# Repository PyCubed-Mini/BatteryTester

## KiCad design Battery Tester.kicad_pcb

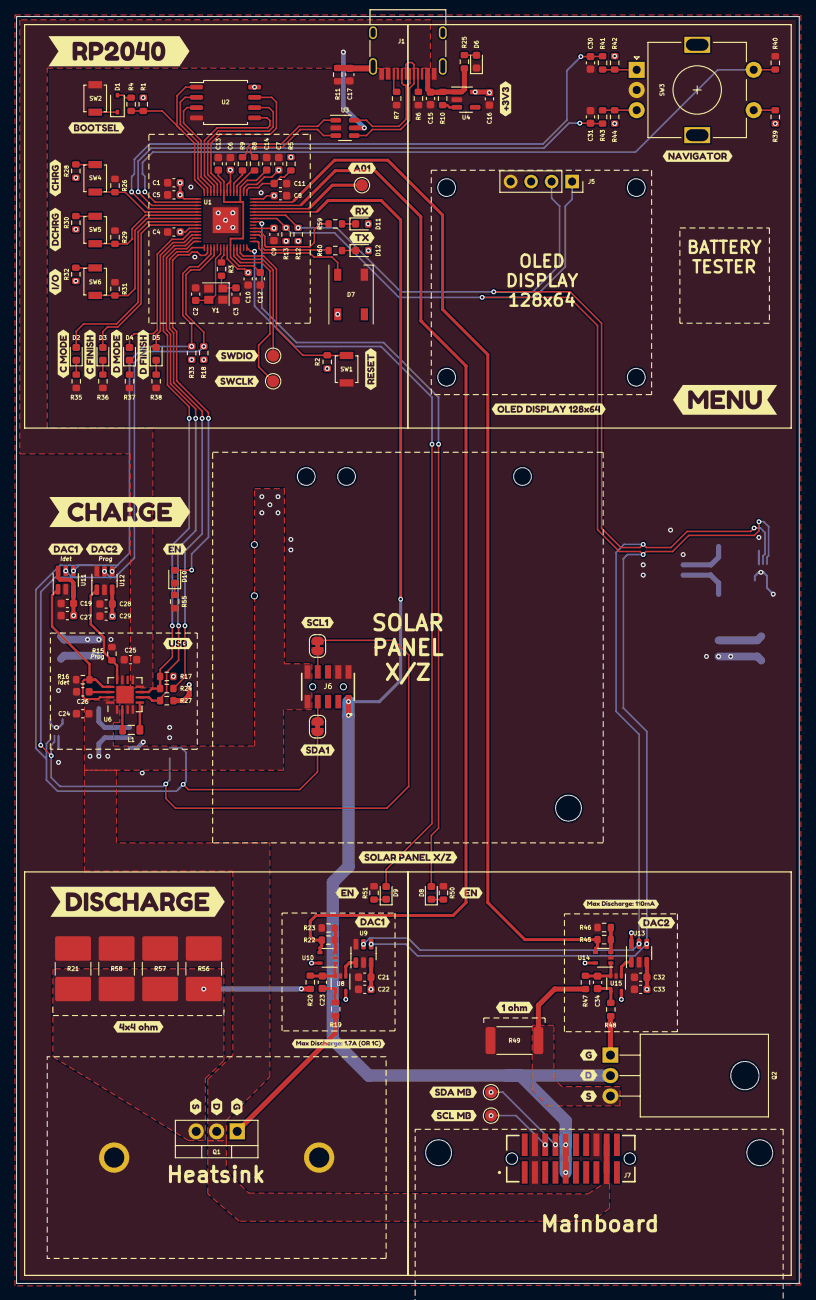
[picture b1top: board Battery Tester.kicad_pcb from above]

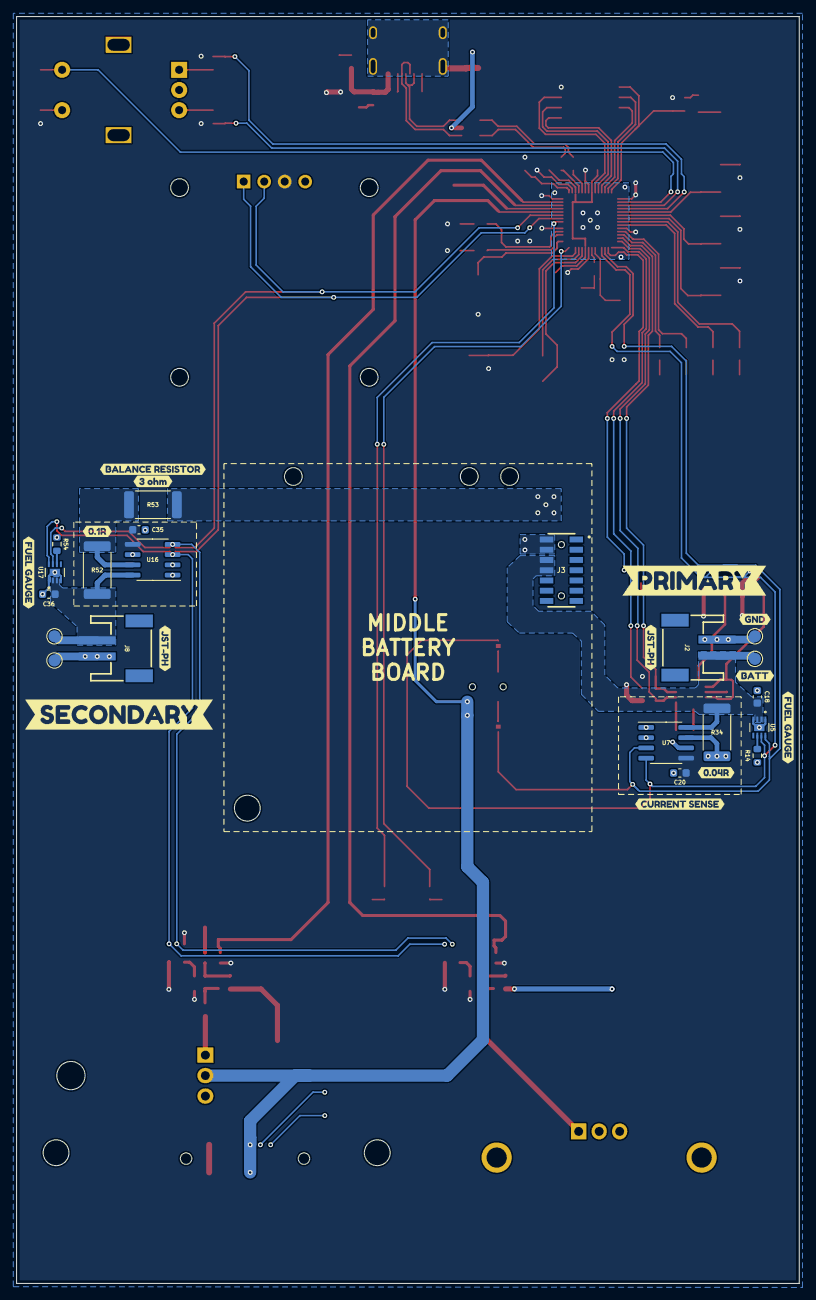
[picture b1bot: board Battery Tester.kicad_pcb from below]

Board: 2 copper layers, 97.0 x 157.0 mm, 212 parts (33 on the bottom side), 99 nets.

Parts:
C1, C11, C12, C15, C16, C18, C36: 1uF; C_0603_1608Metric
C2, C3: 22pF; C_0603_1608Metric
C4, C5, C6, C7, C8, C9, C10, C13, C14, C19, C20, C21, C26, C28, C32, C35: 0.1uF; C_0603_1608Metric
C17: 4.7nF; C_0603_1608Metric
C22, C23, C24, C25, C27, C29, C33, C34: 10uF; C_0603_1608Metric
C30, C31: 0.01uF; C_0603_1608Metric
D1: D_Schottky; D_SOD-323
D2, D3, D4, D5, D11, D12: Amber; LED_0603_1608Metric
D6: Green; LED_0603_1608Metric
D7: WS2812B; LED_WS2812B_PLCC4_5.0x5.0mm_P3.2mm
D8, D9, D10: Blue; LED_0603_1608Metric
HS2: Heatsink_Pad; RAT2X38E
J1: USB-C Receptacle; USB_C_Receptacle_HRO_TYPE-C-31-M-12
J2, J8: JST-PH; JSTPH2
J3: FLE-107-01-X-DV-A; SAMTEC_FLE-107-01-X-DV-A
J5: OLED DISPLAY; PinSocket_1x04_P2.54mm_Vertical
J6: FLE-105-01-X-DV-A; SAMTEC_FLE-105-01-X-DV-A
J7: TFM-110-12-X-D-A; SAMTEC_TFM-110-12-X-D-A
JP1, JP2: Jumper_2_Bridged; SolderJumper-2_P1.3mm_Bridged_RoundedPad1.0x1.5mm
L1: L_Small; L_0805_2012Metric
Q1: IRF540N; TO-220-3_Vertical
Q2: IRF540N; TO-220-3_Horizontal_TabDown
R1, R2, R12, R13, R14, R18, R26, R27, R29, R31, R33, R40, R41, R42, R43, R44, R54: 10K; R_0603_1608Metric
R3, R4, R23, R25, R35, R36, R37, R38, R46, R50, R51, R55, R59, R60: 1K; R_0603_1608Metric
R5, R19, R20, R22, R45, R47, R48: 0; R_0603_1608Metric
R6, R7: 5.1K; R_0603_1608Metric
R8, R9: 27.4; R_0603_1608Metric
R10: 100K; R_0603_1608Metric
R11: 1M; R_0603_1608Metric
R15: R_prog; R_0603_1608Metric
R16: R_idet; R_0603_1608Metric
R17: 390R; R_0603_1608Metric
R21, R56, R57, R58: 4; R_2816_7142Metric
R24, R28, R30, R32, R39: 2K; R_0603_1608Metric
R34: 0.04R; R_2512_6332Metric
R49: 1; R_2512_6332Metric
R52: 0.1R; R_2512_6332Metric
R53: 3R; R_2512_6332Metric
Ref**: Val**; pycubed_mini_half
SW1: Reset; SW_SPST_B3U-1000P
SW2: BOOTSEL; SW_SPST_B3U-1000P
SW3: RotaryEncoder_Switch; RotaryEncoder_Alps_EC11E-Switch_Vertical_H20mm
SW4: Start/Stop; SW_SPST_B3U-1000P
SW5: Charge; SW_SPST_B3U-1000P
SW6: Discharge; SW_SPST_B3U-1000P
TP1: SCL1_MB; TestPoint_Pad_D1.5mm
TP2: SDA1_MB; TestPoint_Pad_D1.5mm
TP3: SWDIO; TestPoint_Pad_D1.5mm
TP4: SWCLK; TestPoint_Pad_D1.5mm
TP5: A01; TestPoint_Pad_D1.5mm
TP6: BATT_SENS; TestPoint_Pad_D1.5mm
TP7, TP9: GND; TestPoint_Pad_D1.5mm
TP8: BATT_SENS_2; TestPoint_Pad_D1.5mm
U1: RP2040; IC57_RP2040
U2: W25Q32JVSS; SOIC-8_5.23x5.23mm_P1.27mm
U3: USBLC6-2SC6; SOT-23-6
U4: AP2112K-3.3; SOT-23-5
U5, U17: MAX17048G
U6: LTC4001; QFN-16-1EP_4x4mm_P0.65mm_EP2.15x2.15mm
U7, U16: INA219BxD; SOIC-8_3.9x4.9mm_P1.27mm
U8, U10, U14, U15: TLV9001IDCK; SOT-353_SC-70-5
U9, U11, U12, U13: MCP4725xxx-xCH; SOT-23-6
Y1: 12MHz; Crystal_SMD_2520-4Pin_2.5x2.0mm
kibuzzard-643A0FFF: G***; kibuzzard-643A0FFF
kibuzzard-643A06C8: G***; kibuzzard-643A06C8
kibuzzard-643A08B7: G***; kibuzzard-643A08B7
kibuzzard-643A09FA, kibuzzard-643A09FA#2, kibuzzard-643A09FA#3: G***; kibuzzard-643A09FA
kibuzzard-643A070F: G***; kibuzzard-643A070F
kibuzzard-643A089C: G***; kibuzzard-643A089C
kibuzzard-643A091C: G***; kibuzzard-643A091C
kibuzzard-643A0700, kibuzzard-643A0700#2: G***; kibuzzard-643A0700
kibuzzard-643A0912: G***; kibuzzard-643A0912
kibuzzard-643CBBC0: G***; kibuzzard-643CBBC0
kibuzzard-6438A1B5: G***; kibuzzard-6438A1B5
kibuzzard-6438A1DA: G***; kibuzzard-6438A1DA
kibuzzard-6438A1E8: G***; kibuzzard-6438A1E8
kibuzzard-6438A2F8: G***; kibuzzard-6438A2F8
kibuzzard-6438A03B: G***; kibuzzard-6438A03B
kibuzzard-6438A05A: G***; kibuzzard-6438A05A
kibuzzard-6438A06A: G***; kibuzzard-6438A06A
kibuzzard-6438A12F: G***; kibuzzard-6438A12F
kibuzzard-6438A59C: G***; kibuzzard-6438A59C
kibuzzard-6438A119: G***; kibuzzard-6438A119
kibuzzard-6438A146: G***; kibuzzard-6438A146
kibuzzard-6438A591: G***; kibuzzard-6438A591
kibuzzard-6438B7A5: G***; kibuzzard-6438B7A5
kibuzzard-6438B33D: G***; kibuzzard-6438B33D
kibuzzard-6438B93A: G***; kibuzzard-6438B93A
kibuzzard-6438B767: G***; kibuzzard-6438B767
kibuzzard-6445C5A7: G***; kibuzzard-6445C5A7
kibuzzard-6445C9CC: G***; kibuzzard-6445C9CC
kibuzzard-6445C801: G***; kibuzzard-6445C801
kibuzzard-6445CB82: G***; kibuzzard-6445CB82
kibuzzard-6445CBB2: G***; kibuzzard-6445CBB2
kibuzzard-6445CBC6: G***; kibuzzard-6445CBC6
kibuzzard-6445CBEB: G***; kibuzzard-6445CBEB
kibuzzard-6445CC4D, kibuzzard-6445CC4D#2: G***; kibuzzard-6445CC4D
kibuzzard-6445CC26: G***; kibuzzard-6445CC26
kibuzzard-6445CCAB, kibuzzard-6445CCAB#2: G***; kibuzzard-6445CCAB
kibuzzard-6445CCB6, kibuzzard-6445CCB6#2: G***; kibuzzard-6445CCB6
kibuzzard-6445CDE6: G***; kibuzzard-6445CDE6
kibuzzard-6445CE6B: G***; kibuzzard-6445CE6B
kibuzzard-6445CE94: G***; kibuzzard-6445CE94
kibuzzard-6445CEE7, kibuzzard-6445CEE7#2: G***; kibuzzard-6445CEE7
kibuzzard-6445CF1E, kibuzzard-6445CF1E#2: G***; kibuzzard-6445CF1E
kibuzzard-6445CFA2: G***; kibuzzard-6445CFA2
kibuzzard-6445CFCB: G***; kibuzzard-6445CFCB
kibuzzard-6445D55B: G***; kibuzzard-6445D55B
kibuzzard-6445D503: G***; kibuzzard-6445D503
kibuzzard-6445D545: G***; kibuzzard-6445D545
kibuzzard-64389E8B: G***; kibuzzard-64389E8B
kibuzzard-64389EC9: G***; kibuzzard-64389EC9

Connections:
3V3_SP: J6.1, J7.9, J7.10, Q2.2 (D), U1.38 (GPIO26/ADC0)
+1V1: C12.1, C13.1, C14.1, U1.23 (DVDD), U1.45 (VREG_VOUT), U1.50 (DVDD)
+3V3: C1.1, C4.1, C5.1, C6.1, C7.1, C8.1, C9.1, C10.1, C16.1, C19.1, C20.1, C21.1, C22.1, C27.1, C28.1, C29.1, C32.1, C33.1, C35.1, D7.1 (VDD), D11.2 (A), D12.2 (A), J5.3, R1.1, R2.1, R5.2, R12.2, R13.2, R17.1, R18.2, R27.2, R28.1, R30.1, R32.1, R33.2, R39.1, R42.2, R44.2, U1.1 (IOVDD), U1.10 (IOVDD), U1.22 (IOVDD), U1.33 (IOVDD), U1.42 (IOVDD), U1.44 (VREG_VIN), U1.48 (USB_VDD), U1.49 (IOVDD), U2.8 (VCC), U4.5 (VOUT), U7.5 (VS), U8.5 (V+), U9.3 (VDD), U10.5 (V+), U11.3 (VDD), U11.6 (A0), U12.3 (VDD), U13.3 (VDD), U13.6 (A0), U14.5 (V+), U15.5 (V+), U16.5 (VS)
+BATT: C24.2, J6.9, J6.10, J7.17, J7.18, Q1.2 (D), R34.2, R53.2, U6.1 (BAT), U6.16 (BATSENS), U7.7 (IN-)
/A01: TP5.1, U1.39 (GPIO27/ADC1)
/A02: R22.1, U1.40 (GPIO28/ADC2), U10.4
/A03: R45.1, U1.41 (GPIO29/ADC3), U14.4
/AREF: C11.2, R5.1, U1.43 (ADC_AVDD)
/D00: R40.1, SW3.S2, U1.2 (GPIO0)
/D01: C31.1, R43.1, U1.3 (GPIO1)
/D02: C30.1, R41.1, U1.4 (GPIO2)
/D03: R26.1, SW4.2 (B), U1.5 (GPIO3)
/D04: R29.1, SW5.2 (B), U1.6 (GPIO4)
/D05: R31.1, SW6.2 (B), U1.7 (GPIO5)
/D06: D2.2 (A), U1.8 (GPIO6)
/D07: D3.2 (A), U1.9 (GPIO7)
/D08: D4.2 (A), U1.11 (GPIO8)
/D09: D5.2 (A), U1.12 (GPIO9)
/D10: R17.2, R24.1, U1.13 (GPIO10), U6.7 (~CHRG)
/D11: R27.1, U1.14 (GPIO11), U6.6 (~EN)
/D12: R24.2, U1.15 (GPIO12)
/D13: D10.2 (A), U1.16 (GPIO13)
/D14: D9.2 (A), U1.28 (GPIO17)
/D15: D8.2 (A), U1.35 (GPIO23)
/DAC1: R16.2, U6.13 (IDET), U6.15 (TIMER), U11.1 (VOUT)
/DAC2: R15.2, U6.12 (PROG), U12.1 (VOUT)
/NEOPIXEL: D7.4 (DIN), U1.29 (GPIO18)
/QSPI_CS: R1.2, R4.1, U1.56 (QSPI_CSN), U2.1 (~CS)
/QSPI_DATA0: U1.53 (QSPI_SD0), U2.5 (DI(IO0))
/QSPI_DATA1: U1.55 (QSPI_SD1), U2.2 (DO(IO1))
/QSPI_DATA2: U1.54 (QSPI_SD2), U2.3 (IO2)
/QSPI_DATA3: U1.51 (QSPI_SD3), U2.7 (IO3)
/QSPI_SCK: U1.52 (QSPI_SCLK), U2.6 (CLK)
/RESET: R2.2, SW1.2 (B), U1.26 (RUN)
/RXLED: R59.1, U1.32 (GPIO21)
/SCL0: J5.2, R12.1, U1.37 (GPIO25), U9.5 (SCL), U13.5 (SCL), U16.4 (SCL), U17.7 (SCL)
/SCL1: JP2.2 (B), R18.1, U1.18 (GPIO15), U5.7 (SCL), U7.4 (SCL), U11.5 (SCL), U12.5 (SCL)
/SDA0: J5.1, R13.1, U1.36 (GPIO24), U9.4 (SDA), U13.4 (SDA), U16.3 (SDA), U17.8 (SDA)
/SDA1: JP1.1 (A), R33.1, U1.17 (GPIO14), U5.8 (SDA), U7.3 (SDA), U11.4 (SDA), U12.4 (SDA)
/SWCLK: TP4.1, U1.24 (SWCLK)
/SWDIO: TP3.1, U1.25 (SWD)
/TXLED: R60.1, U1.31 (GPIO20)
BATT_2: R52.2, R53.1, U16.7 (IN-)
BATT_SENS: C18.1, J2.1, J3.6, J3.8, R34.1, TP6.1, U5.2 (CELL), U5.3 (VDD), U7.8 (IN+)
BATT_SENS_2: C36.1, J8.1, R52.1, TP8.1, U16.8 (IN+), U17.2 (CELL), U17.3 (VDD)
DBus+: J1.A6 (D+), J1.B6 (D+), U3.6 (I/O1)
DBus-: J1.A7 (D-), J1.B7 (D-), U3.4 (I/O2)
DM: R8.2, U1.46 (USB_DM)
DP: R9.1, U1.47 (USB_DP)
GND: C1.2, C2.1, C3.1, C4.2, C5.2, C6.2, C7.2, C8.2, C9.2, C10.2, C11.1, C12.2, C13.2, C14.2, C15.2, C16.2, C17.1, C18.2, C19.2, C20.2, C21.2, C22.2, C24.1, C25.2, C26.1, C27.2, C28.2, C29.2, C30.2, C31.2, C32.2, C33.2, C35.2, C36.2, D6.1 (K), D7.3 (VSS), HS2.1, HS2.2, J1.A1 (GND), J1.A12 (GND), J1.B1 (GND), J1.B12 (GND), J2.2, J3.2, J3.4, J5.4, J6.2, J6.4, J7.3, J7.4, J7.16, J8.2, R6.1, R7.1, R11.2, R14.2, R15.1, R16.1, R21.1, R23.1, R26.2, R29.2, R31.2, R35.1, R36.1, R37.1, R38.1, R40.2, R46.1, R49.1, R50.1, R51.1, R54.2, R55.1, R56.1, R57.1, R58.1, SW1.1 (A), SW2.2 (B), SW3.C, TP7.1, TP9.1, U1.19 (TESTEN), U1.57 (GND), U2.4 (GND), U3.2 (GND), U4.2 (GND), U5.1 (CTG), U5.4 (VSS), U5.9 (PAD), U6.3 (PGND), U6.4 (GNDSENS), U6.11 (NTC), U6.17 (PAD), U7.1 (A1), U7.2 (A0), U7.6 (GND), U8.2 (V-), U9.2 (VSS), U9.6 (A0), U10.2 (V-), U11.2 (VSS), U12.2 (VSS), U12.6 (A0), U13.2 (VSS), U14.2 (V-), U15.2 (V-), U16.1 (A1), U16.2 (A0), U16.6 (GND), U17.1 (CTG), U17.4 (VSS), U17.9 (PAD), Y1.2, Y1.4
unnamed: C3.2, R3.1, Y1.1
unnamed: C23.2, R19.1, U8.4
unnamed: C34.2, R48.1, U15.4
unnamed: D1.2 (A), R4.2
unnamed: D1.1 (K), SW2.1 (A)
unnamed: D2.1 (K), R35.2
unnamed: D3.1 (K), R36.2
unnamed: D4.1 (K), R37.2
unnamed: D5.1 (K), R38.2
unnamed: D6.2 (A), R25.2
unnamed: D8.1 (K), R50.2
unnamed: D9.1 (K), R51.2
unnamed: D10.1 (K), R55.2
unnamed: D11.1 (K), R59.2
unnamed: D12.1 (K), R60.2
unnamed: J1.A5 (CC1), R6.2
unnamed: J1.B5 (CC2), R7.2
unnamed: C17.2, J1.S1 (SHIELD), R11.1
unnamed: J6.7, JP1.2 (B)
unnamed: J6.8, JP2.1 (A)
unnamed: J7.6, TP1.1
unnamed: J7.8, TP2.1
unnamed: Q1.1 (G), R19.2
unnamed: Q1.3 (S), R20.2, R21.2, R56.2, R57.2, R58.2
unnamed: Q2.1 (G), R48.2
unnamed: Q2.3 (S), R47.2, R49.2
unnamed: R8.1, U3.3 (I/O2)
unnamed: R9.2, U3.1 (I/O1)
unnamed: R39.2, SW3.S1
unnamed: R41.2, R42.1, SW3.A
unnamed: R43.2, R44.1, SW3.B
unnamed: R28.2, SW4.1 (A)
unnamed: R30.2, SW5.1 (A)
unnamed: R32.2, SW6.1 (A)
unnamed: C2.2, U1.20 (XIN), Y1.3
unnamed: R3.2, U1.21 (XOUT)
unnamed: R10.2, U4.3 (EN)
unnamed: R14.1, U5.6 (QSTRT)
unnamed: L1.2, U6.2 (SENSE)
unnamed: C26.2, U6.14 (SS)
unnamed: L1.1, U6.5 (SW)
unnamed: U8.1 (+), U9.1 (VOUT)
unnamed: C23.1, R20.1, U8.3 (-), U10.1 (+)
unnamed: R22.2, R23.2, U10.3 (-)
unnamed: U13.1 (VOUT), U15.1 (+)
unnamed: C34.1, R47.1, U14.1 (+), U15.3 (-)
unnamed: R45.2, R46.2, U14.3 (-)
unnamed: R54.1, U17.6 (QSTRT)
VBUS: C15.1, C25.1, J1.A4 (VBUS), J1.A9 (VBUS), J1.B4 (VBUS), J1.B9 (VBUS), R10.1, R25.1, U3.5 (VBUS), U4.1 (VIN), U6.8 (P_{VIN}), U6.9 (V_{INSENSE})

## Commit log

2023-03-16 Upload files
2023-04-14 Partial Layout Completed
2023-04-15 More routing
2023-04-27 Finished Routing
2023-05-04 Updated gitignore

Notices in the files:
parts and their libraries:
Copyright 2021 Accelerated Designs. All rights reserved.
